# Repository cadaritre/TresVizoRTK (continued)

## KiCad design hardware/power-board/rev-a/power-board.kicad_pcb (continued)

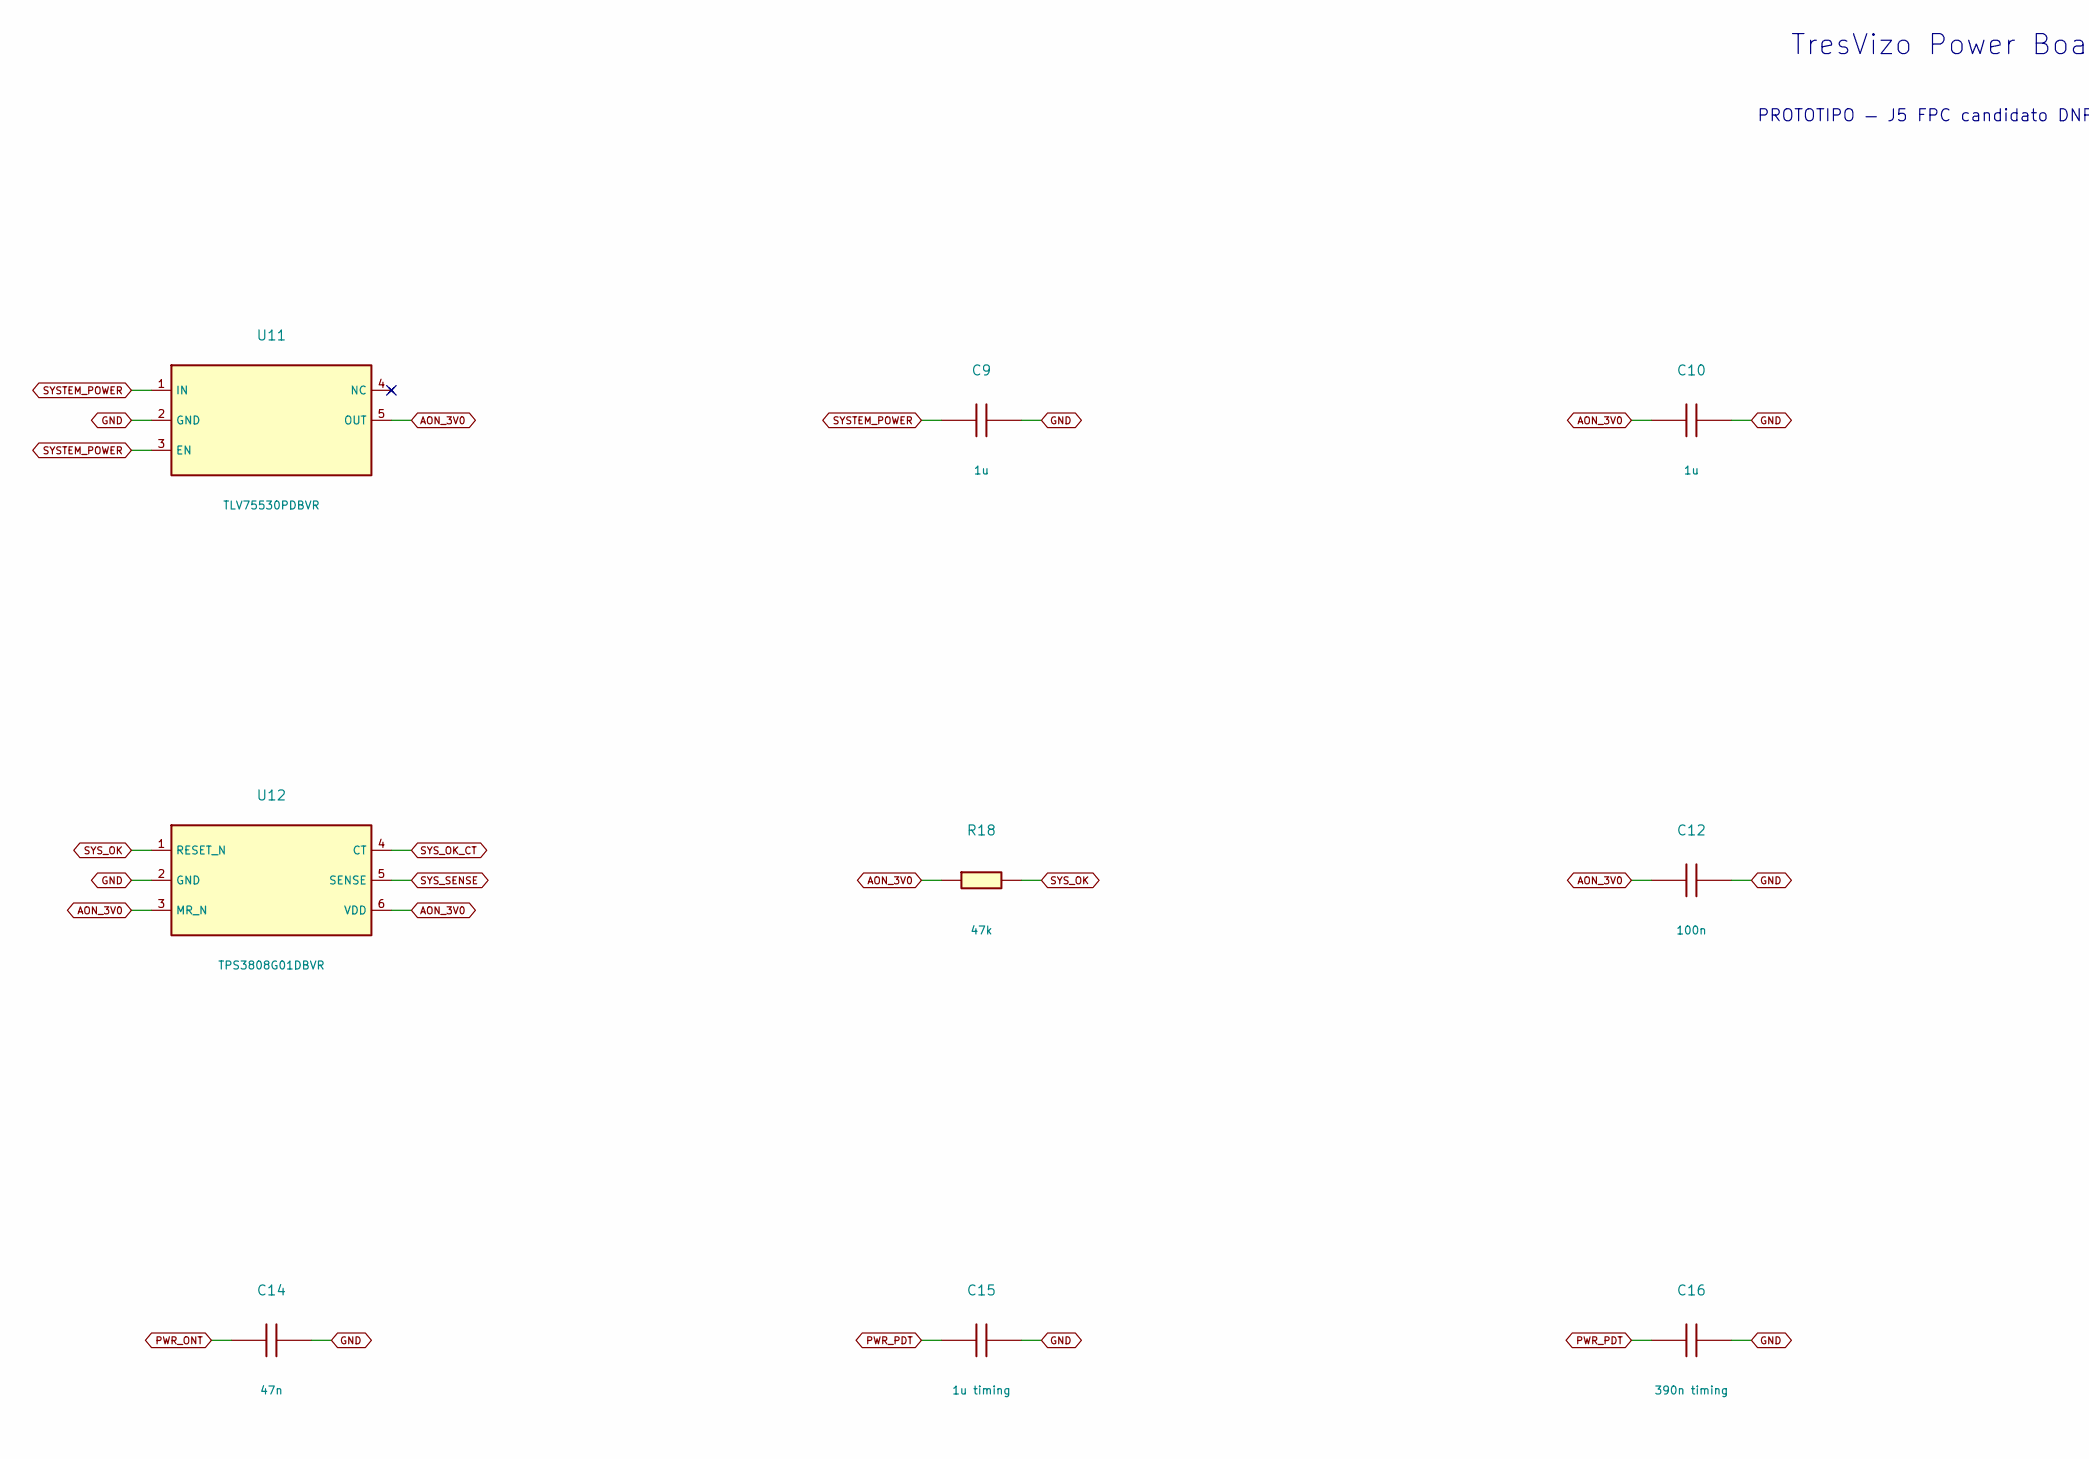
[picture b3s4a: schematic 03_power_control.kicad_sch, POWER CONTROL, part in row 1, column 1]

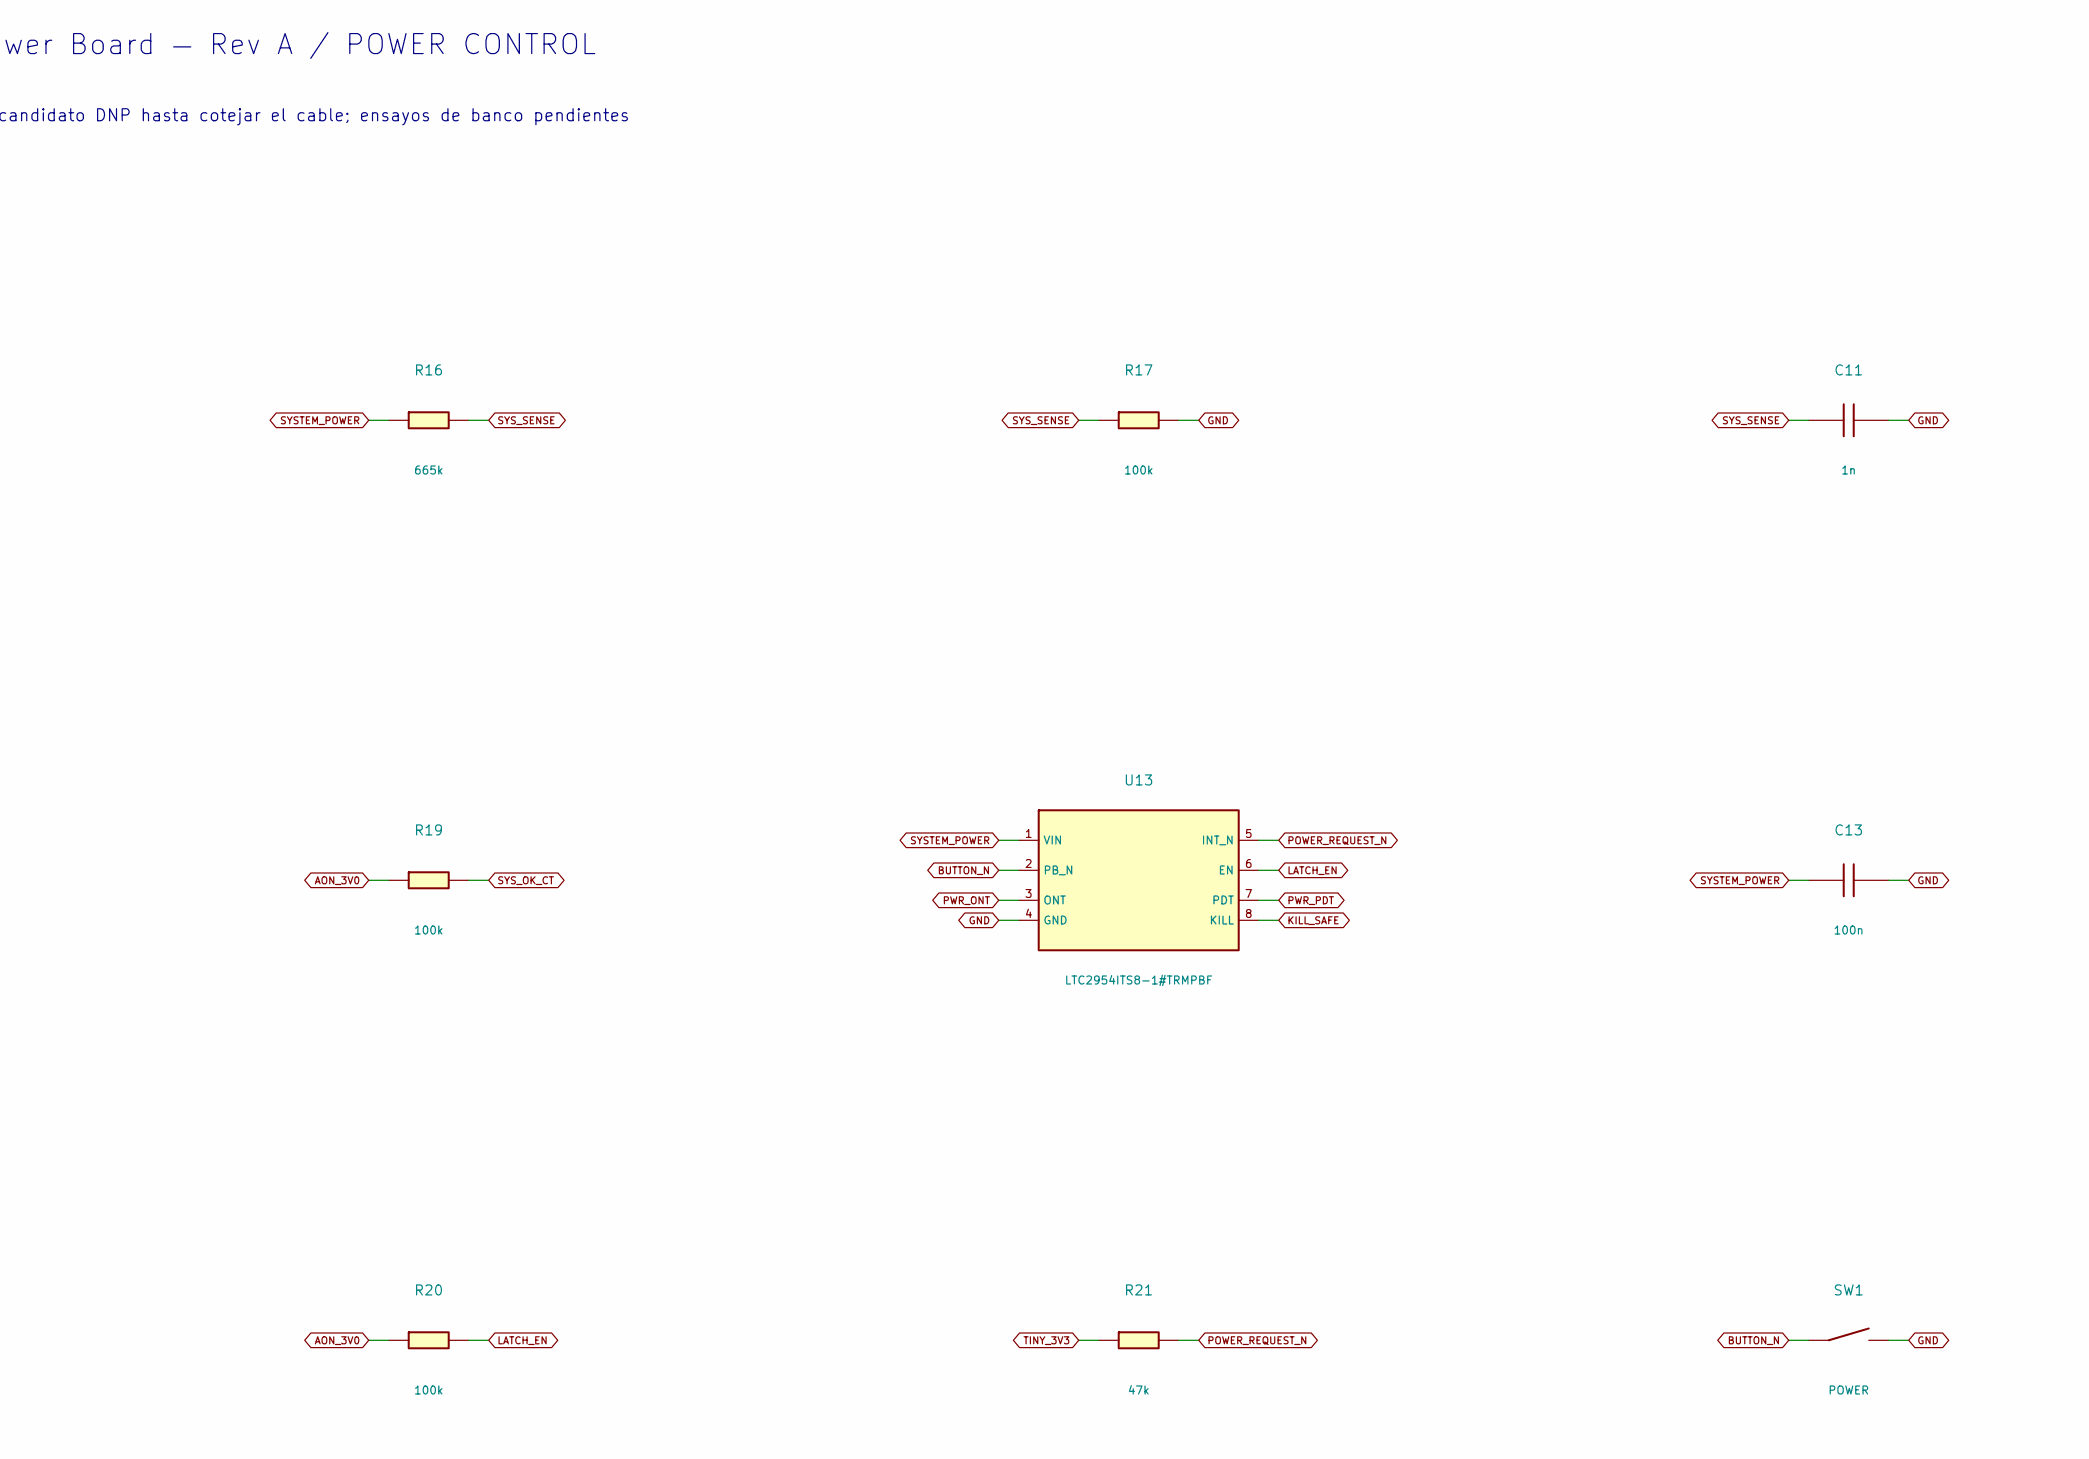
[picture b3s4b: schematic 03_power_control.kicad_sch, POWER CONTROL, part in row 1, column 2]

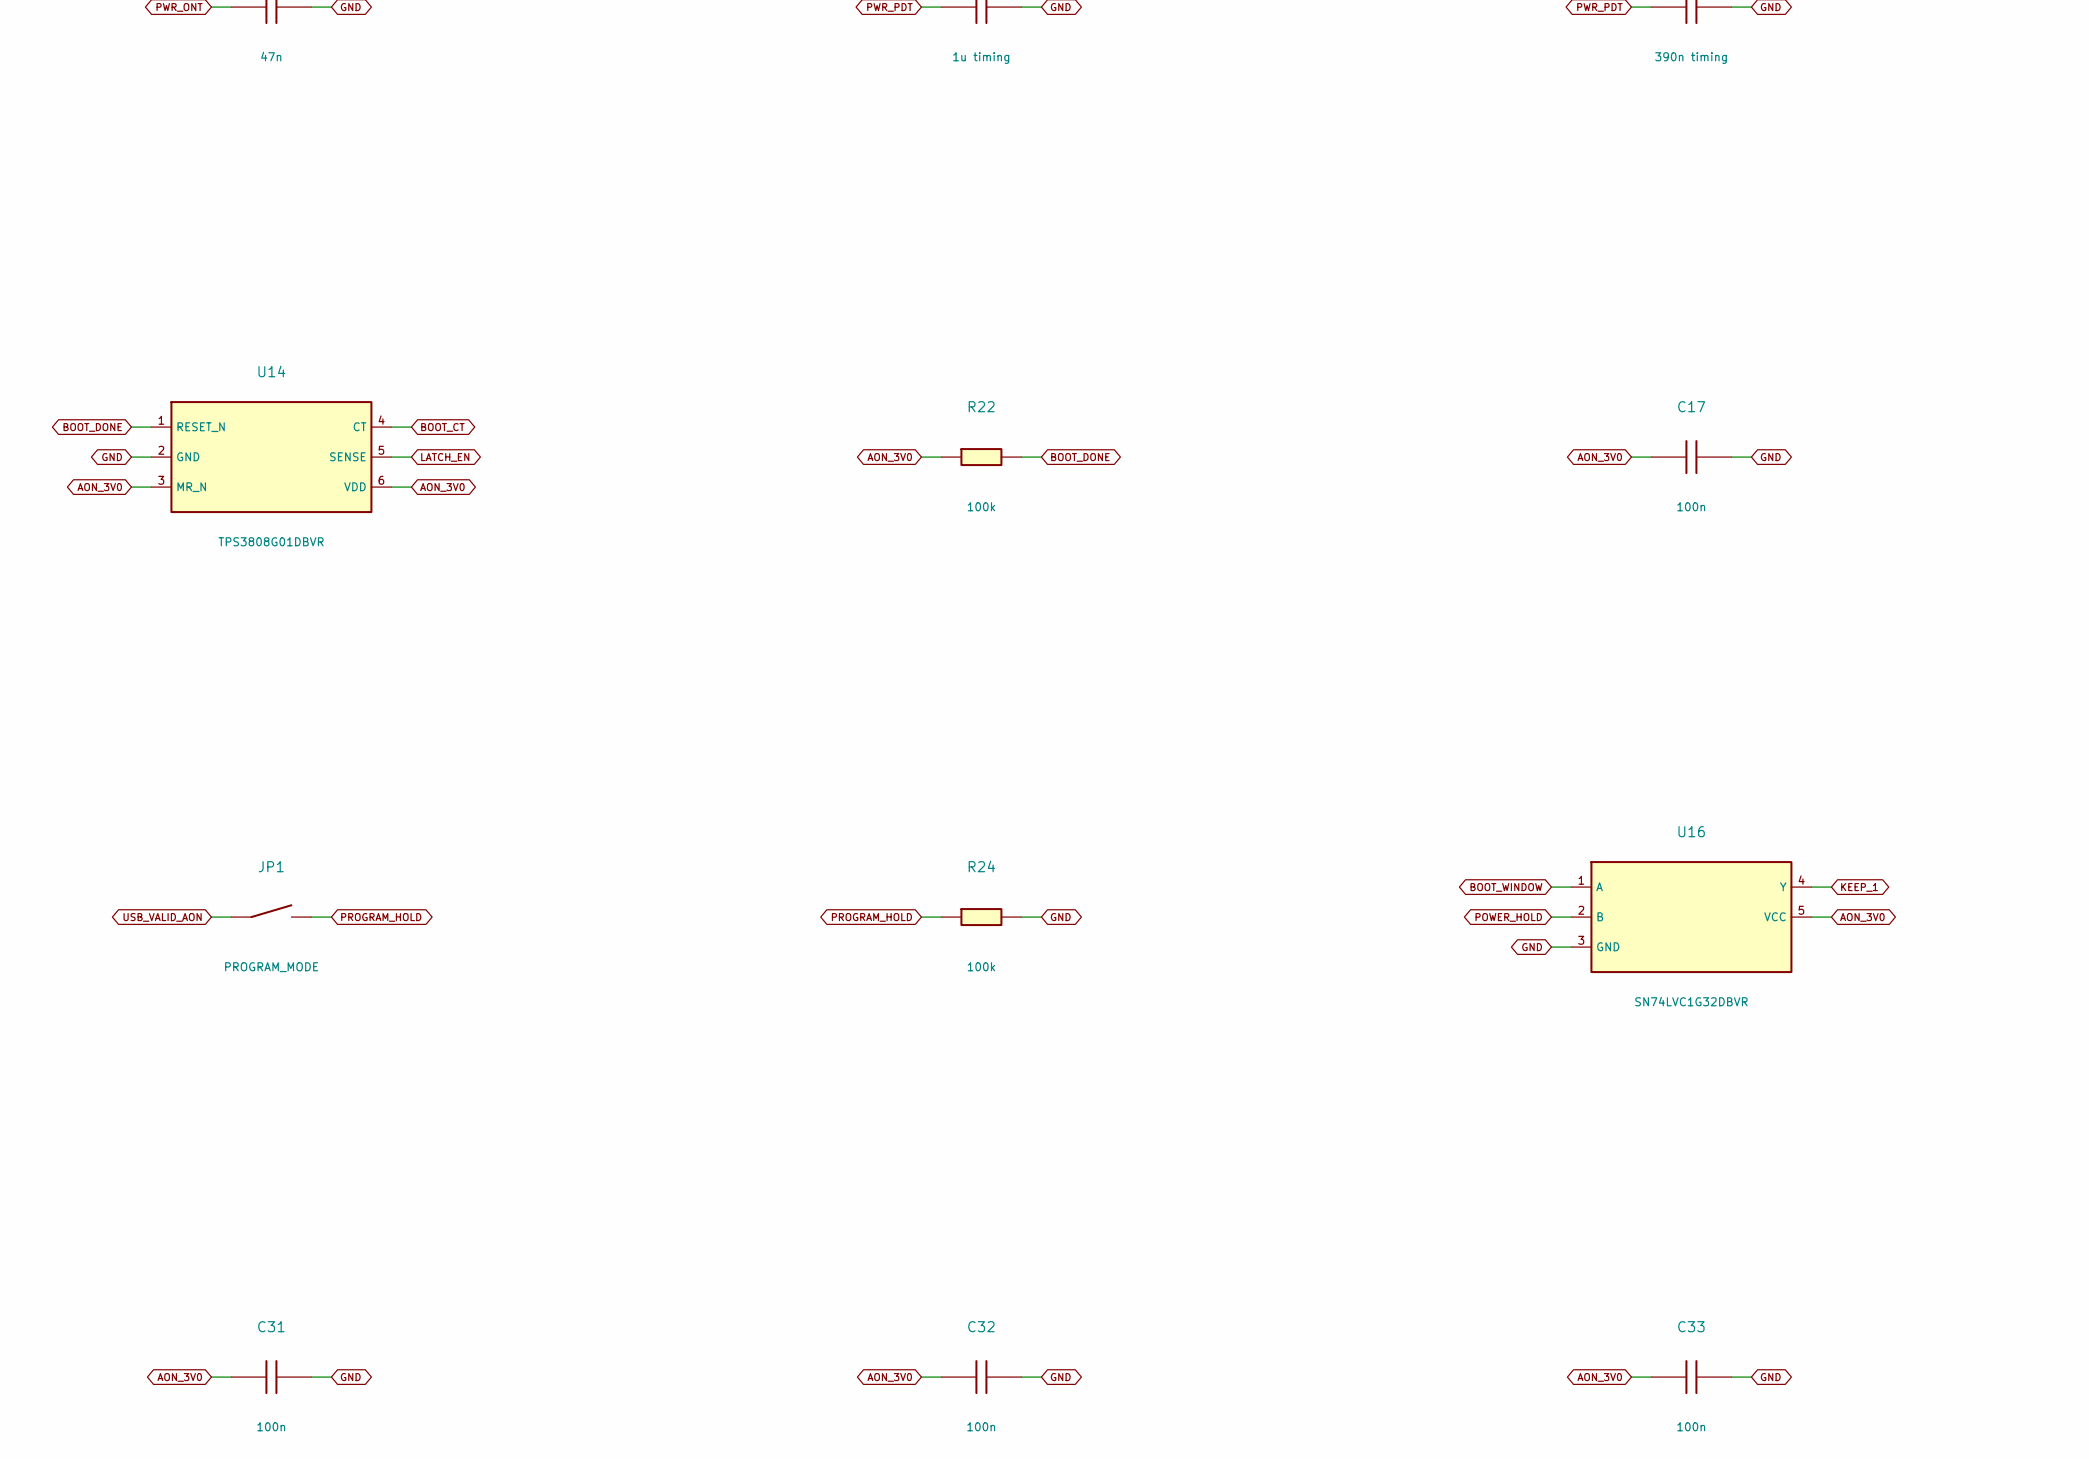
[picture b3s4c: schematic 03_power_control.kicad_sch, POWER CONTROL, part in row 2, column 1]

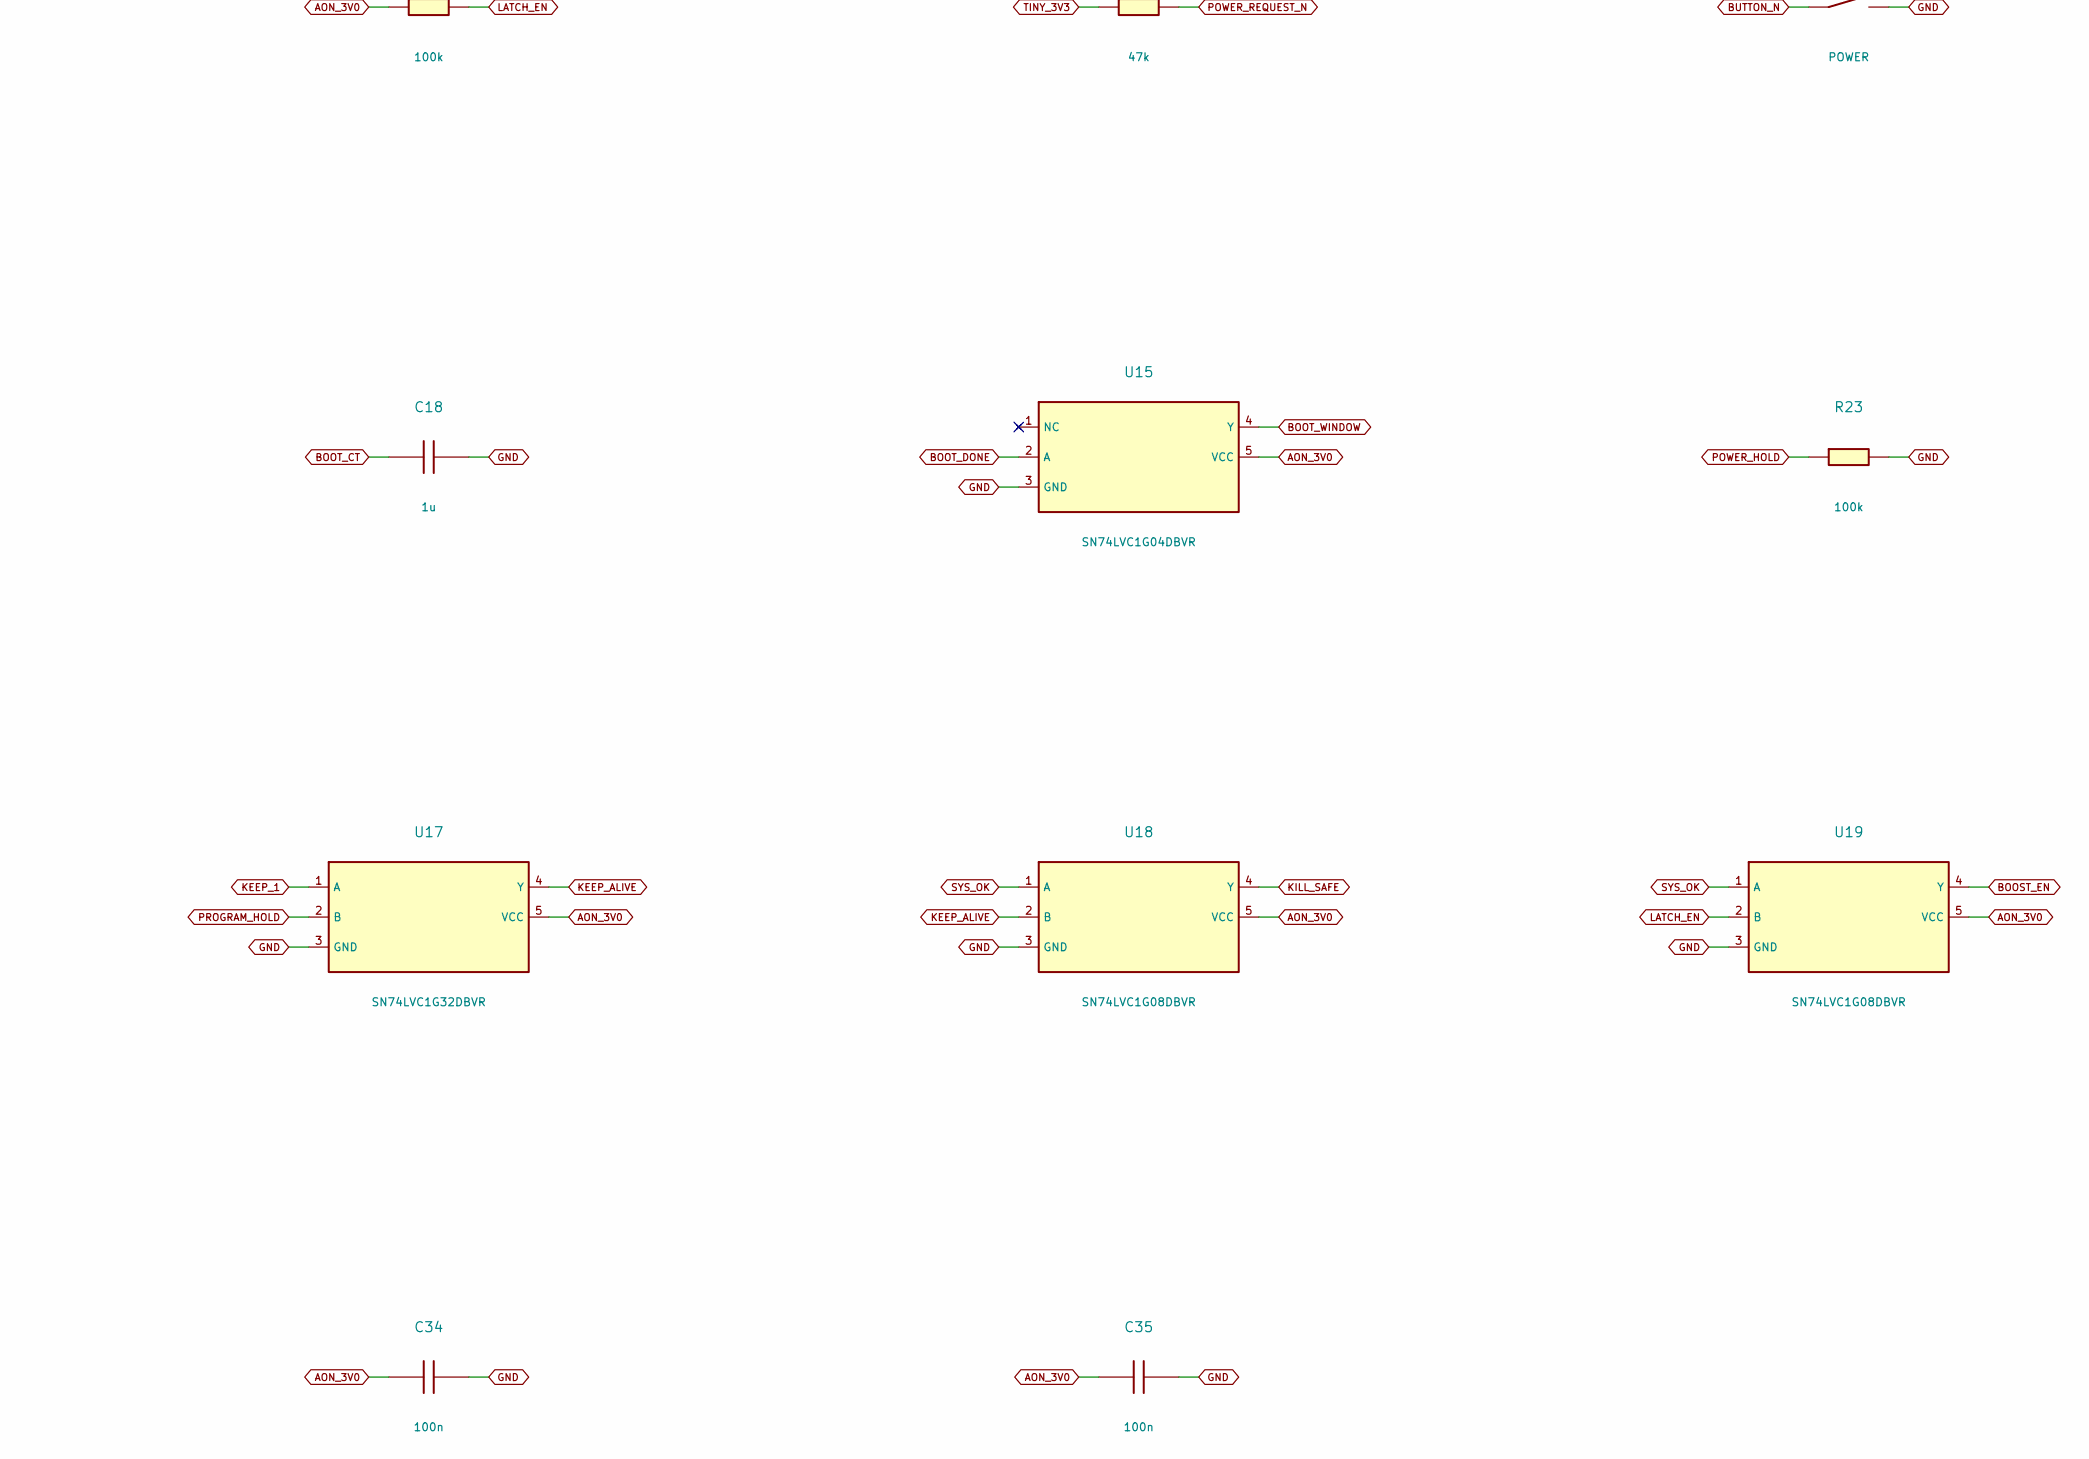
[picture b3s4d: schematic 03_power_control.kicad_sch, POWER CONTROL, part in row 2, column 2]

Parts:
C9, C10, C18: 1u; C_0603_1608Metric; MPN GRM188R71C105KA12D
C11: 1n; C_0603_1608Metric; MPN CC0603KRX7R9BB102
C12, C13, C17, C31, C32, C33, C34, C35: 100n; C_0603_1608Metric; MPN CC0603KRX7R9BB104
C14: 47n; C_0603_1608Metric; MPN CC0603KRX7R9BB473
C15: 1u timing; C_0603_1608Metric; MPN GRM188R71C105KA12D
C16: 390n timing; C_0603_1608Metric; MPN GCM188R71C394KA55D
JP1: PROGRAM_MODE; SolderJumper-2_P1.3mm_Open_Pad1.0x1.5mm; MPN OPEN
R16: 665k; R_0603_1608Metric; MPN RC0603FR-07665KL
R17, R19, R20, R22, R23, R24: 100k; R_0603_1608Metric; MPN RC0603FR-07100KL
R18, R21: 47k; R_0603_1608Metric; MPN RC0603FR-0747KL
SW1: POWER; SW_SPST_TL3305A; MPN TL3305AF160QG
U11: TLV75530PDBVR; SOT-23-5; MPN TLV75530PDBVR
U12, U14: TPS3808G01DBVR; SOT-23-6; MPN TPS3808G01DBVR
U13: LTC2954ITS8-1#TRMPBF; TSOT-23-8; MPN LTC2954ITS8-1#TRMPBF
U15: SN74LVC1G04DBVR; SOT-23-5; MPN SN74LVC1G04DBVR
U16, U17: SN74LVC1G32DBVR; SOT-23-5; MPN SN74LVC1G32DBVR
U18, U19: SN74LVC1G08DBVR; SOT-23-5; MPN SN74LVC1G08DBVR

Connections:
AON_3V0: C10.1, C12.1, C17.1, C31.1, C32.1, C33.1, C34.1, C35.1, R18.1, R19.1, R20.1, R22.1, U11.5 (OUT), U12.3 (MR_N), U12.6 (VDD), U14.3 (MR_N), U14.6 (VDD), U15.5 (VCC), U16.5 (VCC), U17.5 (VCC), U18.5 (VCC), U19.5 (VCC); also elsewhere on the board
BOOST_EN: U19.4 (Y); also elsewhere on the board
BOOT_CT: C18.1, U14.4 (CT)
BOOT_DONE: R22.2, U14.1 (RESET_N), U15.2 (A)
BOOT_WINDOW: U15.4 (Y), U16.1 (A)
BUTTON_N: SW1.1, U13.2 (PB_N)
GND: C9.2, C10.2, C11.2, C12.2, C13.2, C14.2, C15.2, C16.2, C17.2, C18.2, C31.2, C32.2, C33.2, C34.2, C35.2, R17.2, R23.2, R24.2, SW1.2, U11.2 (GND), U12.2 (GND), U13.4 (GND), U14.2 (GND), U15.3 (GND), U16.3 (GND), U17.3 (GND), U18.3 (GND), U19.3 (GND); also elsewhere on the board
KEEP_1: U16.4 (Y), U17.1 (A)
KEEP_ALIVE: U17.4 (Y), U18.2 (B)
KILL_SAFE: U13.8 (KILL), U18.4 (Y); also elsewhere on the board
LATCH_EN: R20.2, U13.6 (EN), U14.5 (SENSE), U19.2 (B)
POWER_HOLD: R23.1, U16.2 (B); also elsewhere on the board
POWER_REQUEST_N: R21.2, U13.5 (INT_N); also elsewhere on the board
PROGRAM_HOLD: JP1.2, R24.1, U17.2 (B)
PWR_ONT: C14.1, U13.3 (ONT)
PWR_PDT: C15.1, C16.1, U13.7 (PDT)
SYSTEM_POWER: C9.1, C13.1, R16.1, U11.1 (IN), U11.3 (EN), U13.1 (VIN); also elsewhere on the board
SYS_OK: R18.2, U12.1 (RESET_N), U18.1 (A), U19.1 (A)
SYS_OK_CT: R19.2, U12.4 (CT)
SYS_SENSE: C11.1, R16.2, R17.1, U12.5 (SENSE)
TINY_3V3: R21.1; also elsewhere on the board
USB_VALID_AON: JP1.1; also elsewhere on the board

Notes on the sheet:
TresVizo Power Board — Rev A / POWER CONTROL
PROTOTIPO — J5 FPC candidato DNP hasta cotejar el cable; ensayos de banco pendientes

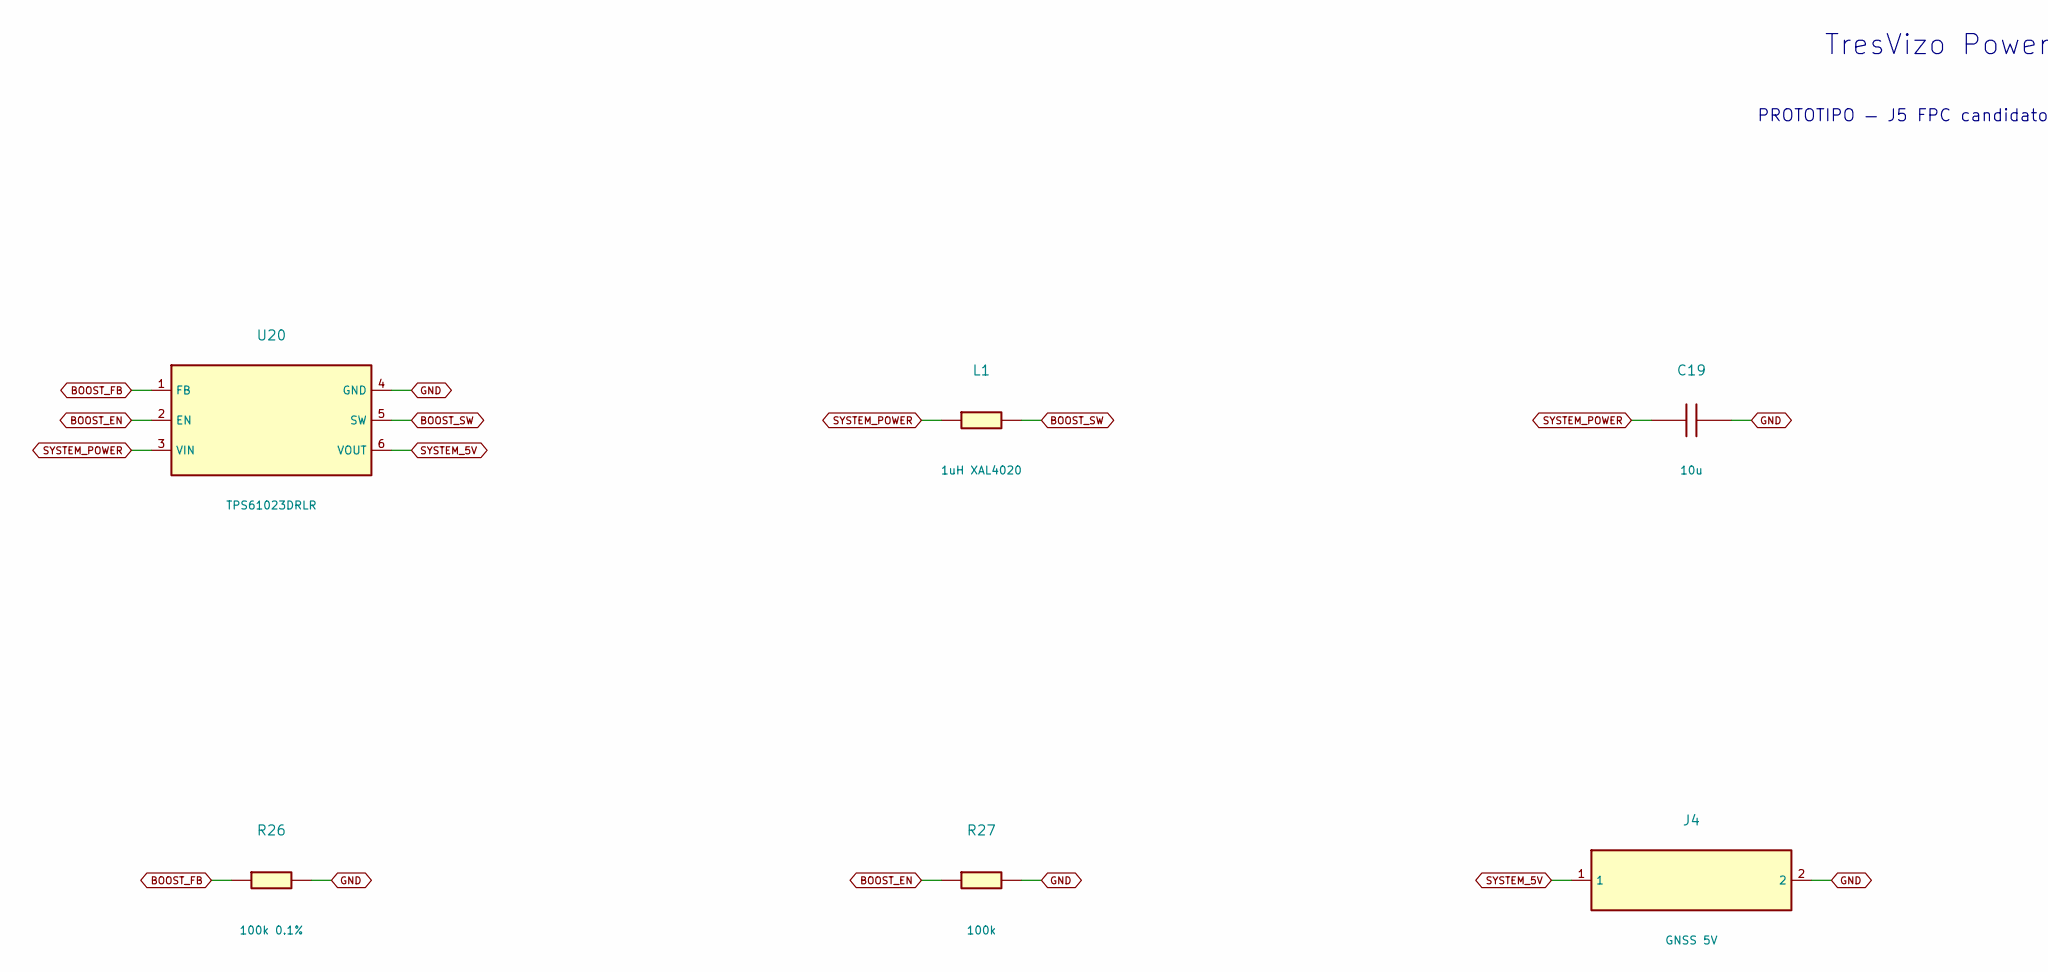
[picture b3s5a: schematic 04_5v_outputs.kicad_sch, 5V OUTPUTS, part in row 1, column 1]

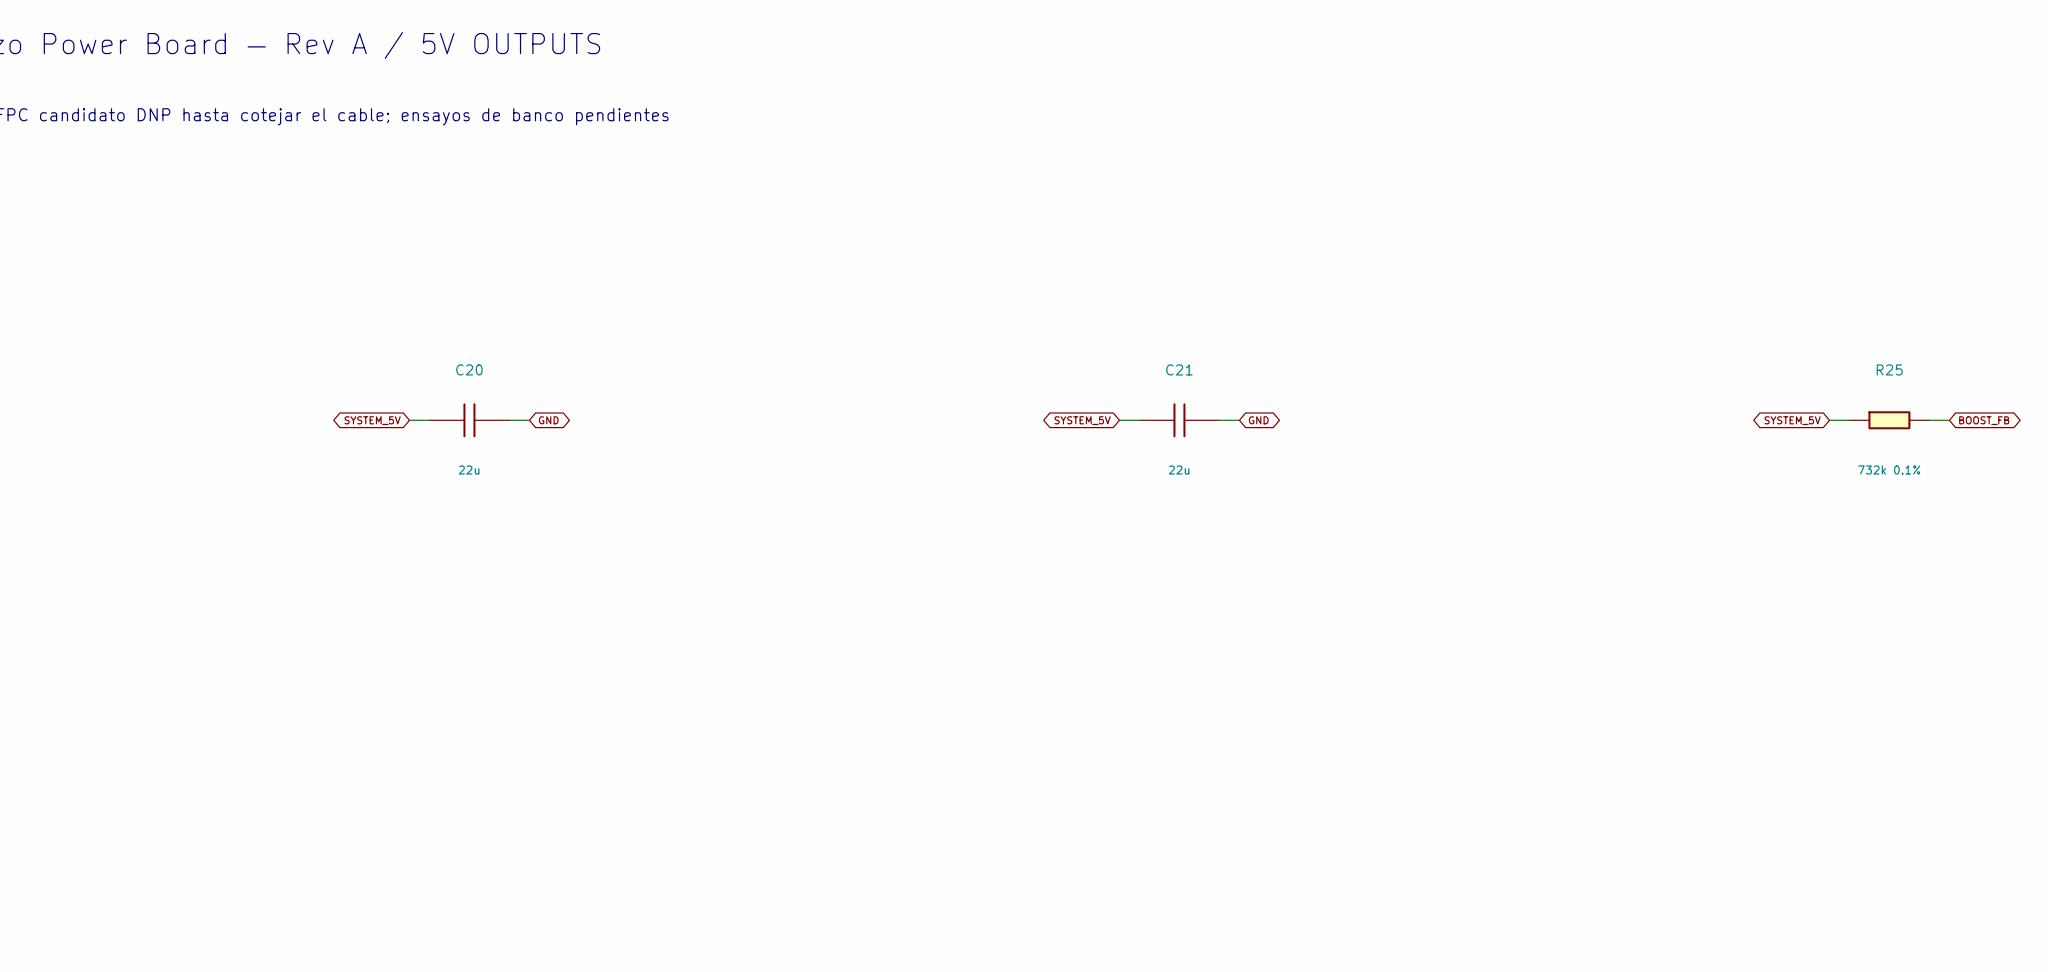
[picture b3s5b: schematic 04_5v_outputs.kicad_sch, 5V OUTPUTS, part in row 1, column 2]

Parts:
C19: 10u; C_0805_2012Metric; MPN GRM21BR71A106KE51L
C20, C21: 22u; C_1206_3216Metric; MPN GRM31CR71A226KE15L
J4: GNSS 5V; JST_PH_S2B-PH-SM4-TB_1x02-1MP_P2.00mm_Horizontal; MPN S2B-PH-SM4-TB(LF)(SN)
L1: 1uH XAL4020; L_Coilcraft_XAL4020-XXX; MPN XAL4020-102MEC
R25: 732k 0.1%; R_0603_1608Metric; MPN RT0603BRD07732KL
R26: 100k 0.1%; R_0603_1608Metric; MPN RT0603BRD07100KL
R27: 100k; R_0603_1608Metric; MPN RC0603FR-07100KL
U20: TPS61023DRLR; SOT-563; MPN TPS61023DRLR

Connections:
BOOST_EN: R27.1, U20.2 (EN); also elsewhere on the board
BOOST_FB: R25.2, R26.1, U20.1 (FB)
BOOST_SW: L1.2, U20.5 (SW)
GND: C19.2, C20.2, C21.2, J4.2, R26.2, R27.2, U20.4 (GND); also elsewhere on the board
SYSTEM_5V: C20.1, C21.1, J4.1, R25.1, U20.6 (VOUT); also elsewhere on the board
SYSTEM_POWER: C19.1, L1.1, U20.3 (VIN); also elsewhere on the board

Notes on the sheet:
TresVizo Power Board — Rev A / 5V OUTPUTS
PROTOTIPO — J5 FPC candidato DNP hasta cotejar el cable; ensayos de banco pendientes
